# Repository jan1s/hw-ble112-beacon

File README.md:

hw-ble112-beacon
================

This is a minimal beacon pcb for the BLE112 module.

Project schematic, the same for both versions.

Render for the uncased version from [DirtyPCB][dirtypcb].

Render for the cased version from [DirtyPCB][dirtypcb].

## BOM
| Identifier | Type/Value | Quantity | Comment | Supplier Id | Supplier |
| ---        | ---        | ---      | ---     | ---         | ---      |
| R1, R2 | 33 Ω | 2 |  | SMD-0603 33  | [Reichelt][reichelt] |
| R3, R4 | 470 Ω | 2 |  | SMD-0603 470 | [Reichelt][reichelt] |
| R5 | 1 kΩ | 2 |  | SMD-0603 1K5 | [Reichelt][reichelt] |
| C2 | 10 nF | 1 |  | X7R-G0603 10N | [Reichelt][reichelt] |
| C1, C3-C6 | 10 µF | 6 |  | X5R-G0603 10/6 | [Reichelt][reichelt] |
| U1 | BLE112 | 1 |  | 603-BLE112-A | [Mouser][mouser] |
| IC1 | LP2985 | 1 |  | LP 2985 IM5-3,3 | [Reichelt][reichelt] |
| X1S | USB Jack | 1 |  | USB BWM SMD | [Reichelt][reichelt] |
| JP3 | 2x5 1.27 | 1 |  | 649-202112100010C4LF | [Mouser][mouser] |
| BT1 | Batteryholder | 1 |  | KZH 20SMD-2 | [Reichelt][reichelt] |
| SW1 | Switch | 1 |  | 1P2T ON-ON type SMD mini slide switch | [Aliexpress][aliexpress] |

[reichelt]: http://www.reichelt.de
[mouser]: http://mouser.com
[aliexpress]: http://www.aliexpress.com

[dirtypcb]: http://dirtypcbs.com
[itead-pcb]: http://imall.iteadstudio.com/open-pcb/pcb-prototyping.html

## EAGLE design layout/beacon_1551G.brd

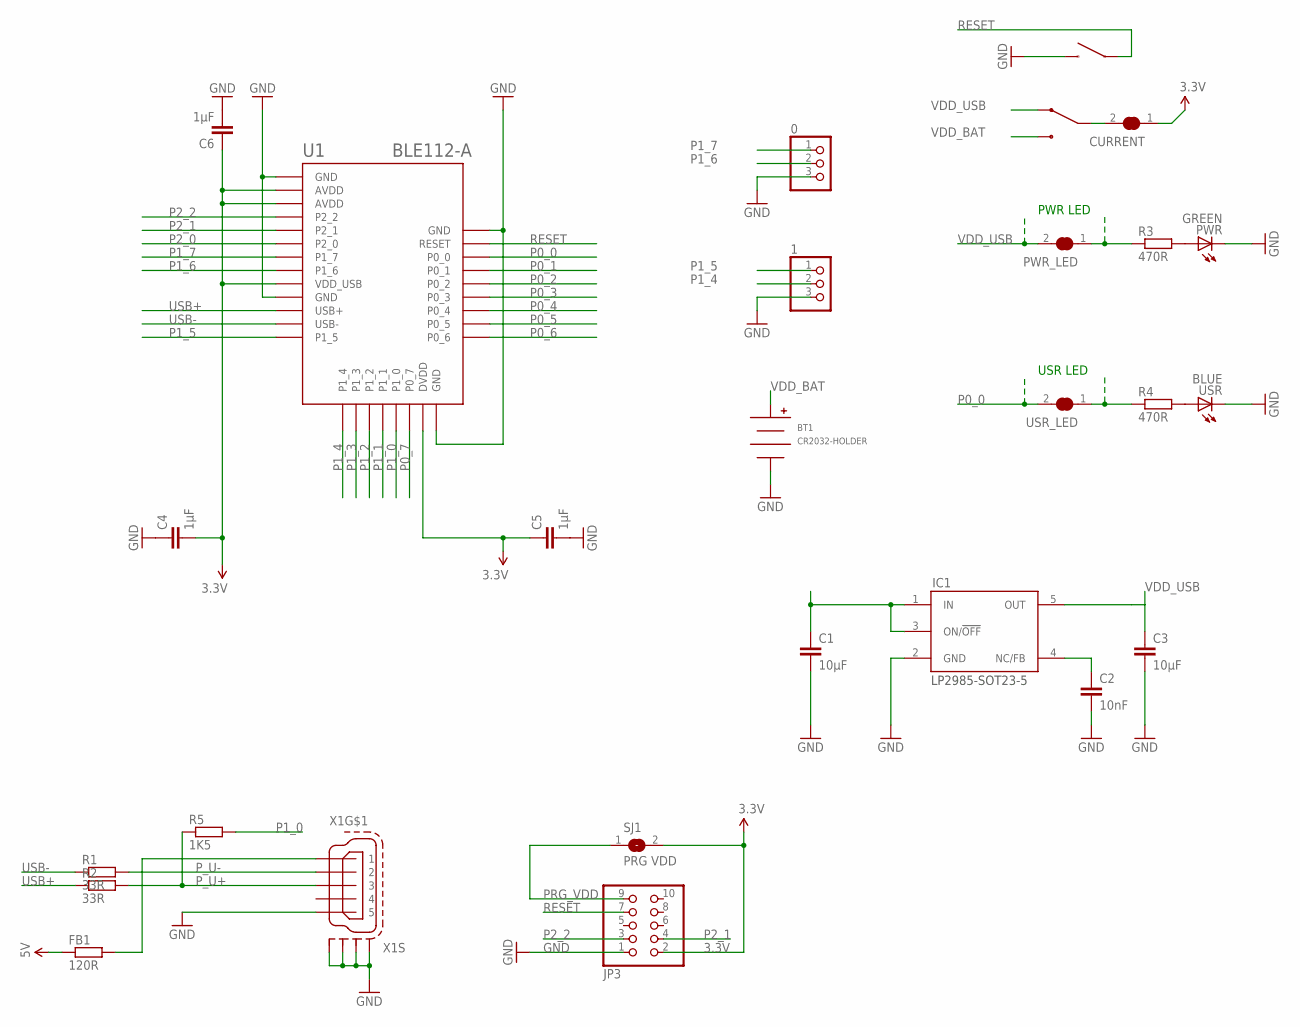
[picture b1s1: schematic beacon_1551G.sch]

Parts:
0, 1: HEADER-1X3ROUND; 1X03_ROUND
BT1: CR2032-HOLDER; CH28-2032LF
C1, C3: 10µF; C0603
C2: 10nF; C0603
C4, C5, C6: 1µF; C0603
CURRENT: SOLDERJUMPER_CLOSED; SOLDERJUMPER_CLOSEDWIRE
FB1: 120R; R0603
IC1: LP2985-SOT23-5; SOT23-5
JP3: ARM-JTAG_1.27-SMD; 20021121-10010XXLF
PWR: GREEN; CHIPLED_0805
PWR_LED: SOLDERJUMPER_CLOSED; SOLDERJUMPER_CLOSEDWIRE
R1, R2: 33R; R0603
R3, R4: 470R; R0603
R5: 1K5; R0603
RST: TACT-SWITCH-40-40; 40-40
SJ1: PRG VDD; SJ
U1: BLE112-A
U$1: 1P2T; 1P2T-ON-ON
USR: BLUE; CHIPLED_0805
USR_LED: SOLDERJUMPER_CLOSED; SOLDERJUMPER_CLOSEDWIRE
X1: MINI-USB-SCHIELD-32005-301; 32005-301

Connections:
3.3V: C4.2, C5.1, C6.1, CURRENT.1, JP3.2, SJ1.2, U1.AVDD1 (AVDD), U1.AVDD2 (AVDD), U1.DVDD, U1.VDD_USB
GND: 0.3, 1.3, BT1.NEG, C1.2, C2.2, C3.2, C4.1, C5.2, C6.2, IC1.2 (GND), JP3.1, PWR.C, RST.1, RST.2, U1.GND1 (GND), U1.GND2 (GND), U1.GND3 (GND), U1.GND4 (GND), USR.C, X1.5, X1.M1 (S1), X1.M2 (S2), X1.M3 (S3), X1.M4 (S4)
unnamed: PWR.A, R3.2
unnamed: R4.2, USR.A
unnamed: PWR_LED.1, R3.1
unnamed: CURRENT.2, U$1.2
unnamed: R4.1, USR_LED.1
unnamed: C2.1, IC1.4 (NC/FB)
P0_0: U1.P0_0, USR_LED.2
P0_1: U1.P0_1
P0_2: U1.P0_2
P0_3: U1.P0_3
P0_4: U1.P0_4
P0_5: U1.P0_5
P0_6: U1.P0_6
P0_7: U1.P0_7
P1_0: R5.2, U1.P1_0
P1_1: U1.P1_1
P1_2: U1.P1_2
P1_3: U1.P1_3
P1_4: 1.2, U1.P1_4
P1_5: 1.1, U1.P1_5
P1_6: 0.2, U1.P1_6
P1_7: 0.1, U1.P1_7
P2_0: U1.P2_0
P2_1: JP3.4, U1.P2_1
P2_2: JP3.3, U1.P2_2
PRG_VDD: JP3.9, SJ1.1
P_U+: R2.2, R5.1, X1.3
P_U-: R1.2, X1.2
RESET: JP3.7, RST.3, RST.4, U1.RESET
USB+: R2.1, U1.USB+
USB-: R1.1, U1.USB-
VBUS: FB1.2, X1.1
VDD_BAT: BT1.POS, U$1.3
VDD_USB: C3.1, IC1.5 (OUT), PWR_LED.2, U$1.1

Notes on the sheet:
PWR LED
USR LED

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
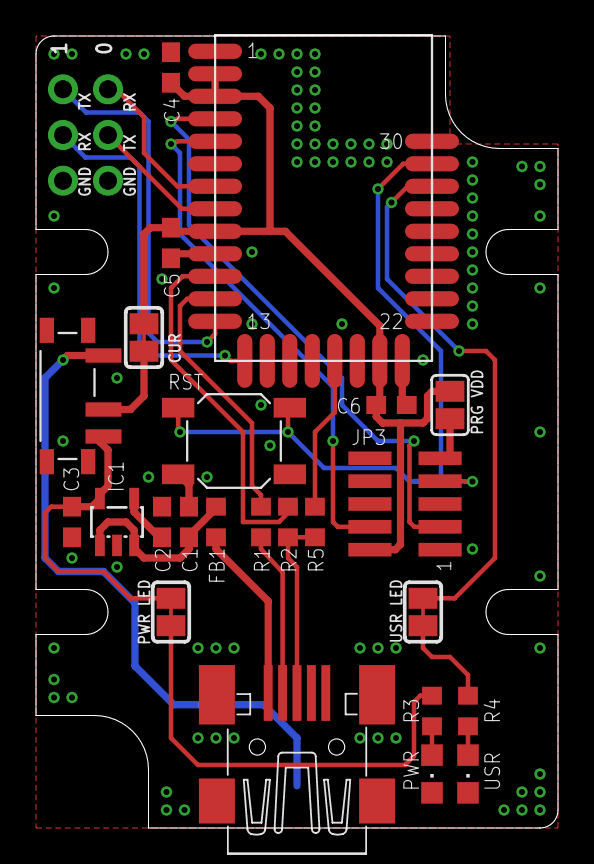
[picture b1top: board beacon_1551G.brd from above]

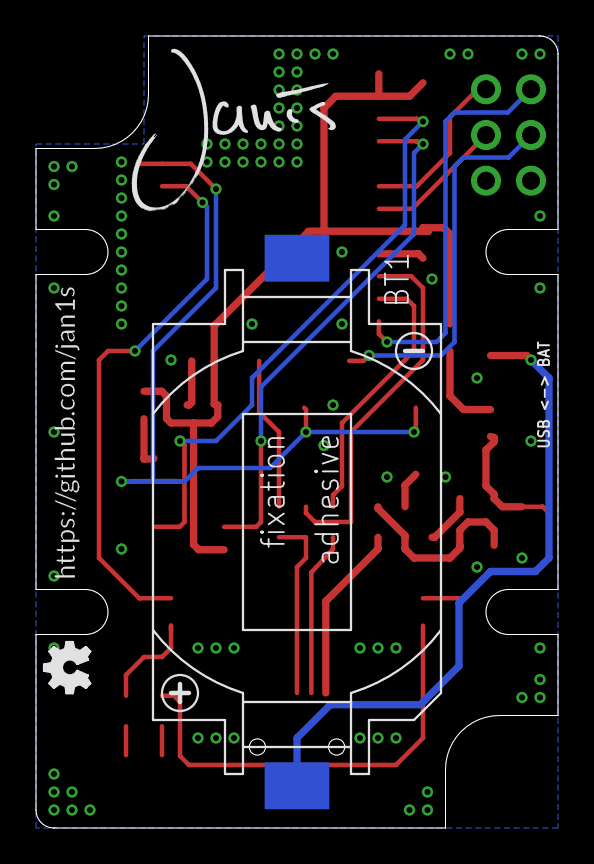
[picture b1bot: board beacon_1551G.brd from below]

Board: 2 copper layers, 29.0 x 44.0 mm, 30 parts (4 on the bottom side), 26 nets.

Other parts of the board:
U$2: JANIS_10MM
U$4: GITHUB/JAN1S
U$5: OSHW_FILLX100_NOTEXT

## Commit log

2014-07-21 Added battery option
2014-07-21 Added production files
2014-07-21 Minor readme fix
2014-07-21 Minor fix
2014-09-03 Added 1551G version
2014-09-03 Changed README
2014-09-03 Changed README DPCB link
2014-09-03 Added uncased version docu
2014-09-03 Added docu schematic

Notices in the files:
parts and their libraries:
microbuilder: This work is placed in the public domain, and may be freely used for commercial and non-commercial work with the following conditions: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
SparkFun: Licensing: CC v3.0 Share-Alike You are welcome to use this library for commercial purposes.
